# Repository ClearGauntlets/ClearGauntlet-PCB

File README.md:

# ClearGauntlet-PCB
PCB - Schematics Design for VR Gloves

A breakout board for ClearGauntlets, aimed at improving cable management and minifying electronics of VR Gloves.

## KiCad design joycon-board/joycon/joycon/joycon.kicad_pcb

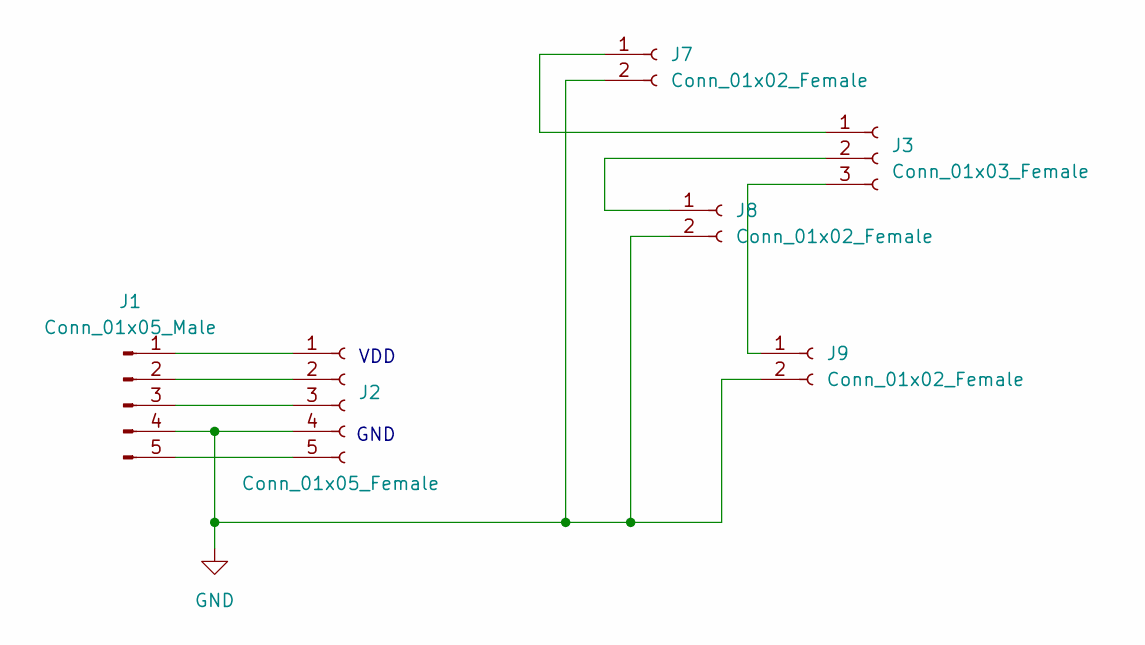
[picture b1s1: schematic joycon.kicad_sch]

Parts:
J1: Conn_01x05_Male; 5034800540
J2: Conn_01x05_Female; PinSocket_1x05_P2.54mm_Vertical
J3: Conn_01x03_Female; PinSocket_1x03_P2.54mm_Vertical
J7, J8, J9: Conn_01x02_Female; PinSocket_1x02_P2.54mm_Vertical

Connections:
GND: J1.4, J2.4, J7.2, J8.2, J9.2
unnamed: J1.1, J2.1
unnamed: J1.2, J2.2
unnamed: J1.3, J2.3
unnamed: J1.5, J2.5
unnamed: J3.1, J7.1
unnamed: J3.2, J8.1
unnamed: J3.3, J9.1

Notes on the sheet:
GND
VDD

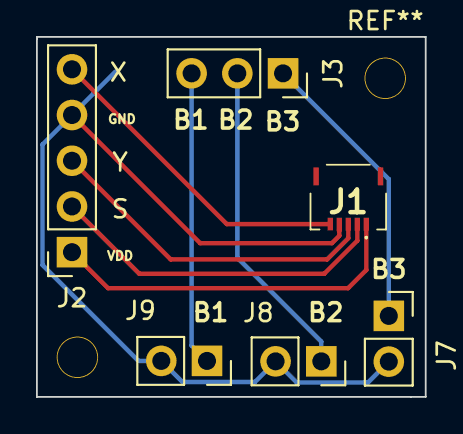
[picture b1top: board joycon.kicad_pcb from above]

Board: 2 copper layers, 21.6 x 20.0 mm, 6 parts (0 on the bottom side), 8 nets.

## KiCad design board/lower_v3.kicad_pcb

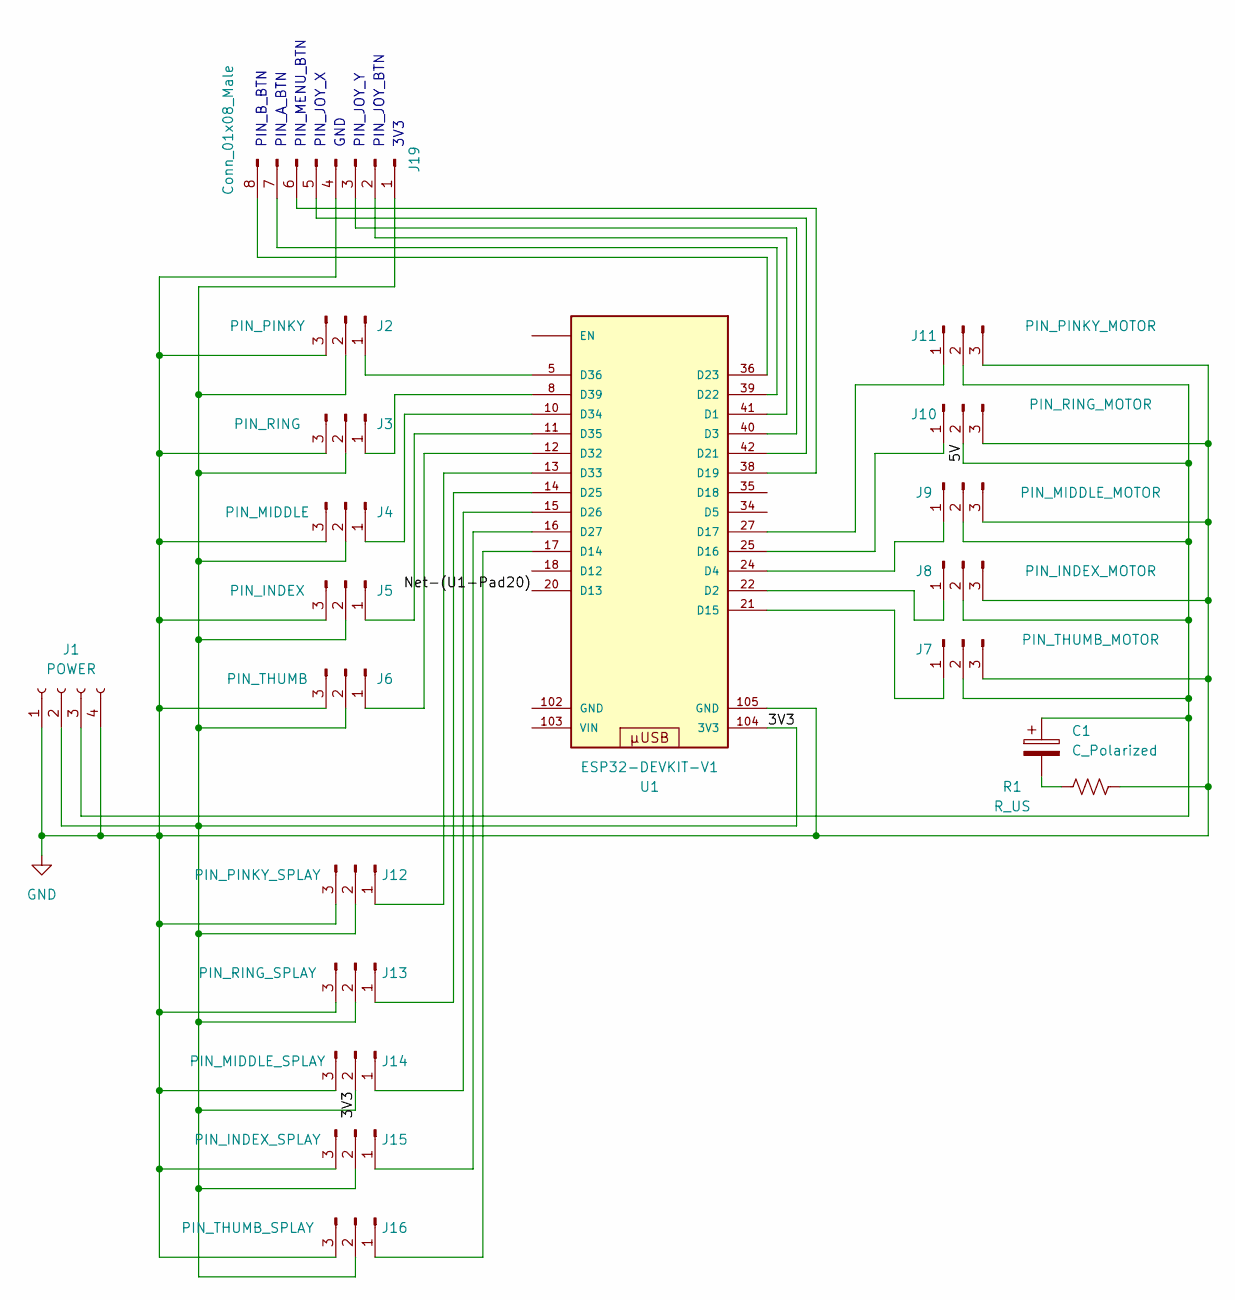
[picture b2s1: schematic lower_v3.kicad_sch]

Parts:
C1: C_Polarized; CP_Radial_D10.0mm_P5.00mm
J1: POWER; JST_EH_B4B-EH-A_1x04_P2.50mm_Vertical
J2: PIN_PINKY; PinHeader_1x03_P2.54mm_Vertical
J3: PIN_RING; PinHeader_1x03_P2.54mm_Vertical
J4: PIN_MIDDLE; PinHeader_1x03_P2.54mm_Vertical
J5: PIN_INDEX; PinHeader_1x03_P2.54mm_Vertical
J6: PIN_THUMB; PinHeader_1x03_P2.54mm_Vertical
J7: PIN_THUMB_MOTOR; PinHeader_1x03_P2.54mm_Vertical
J8: PIN_INDEX_MOTOR; PinHeader_1x03_P2.54mm_Vertical
J9: PIN_MIDDLE_MOTOR; PinHeader_1x03_P2.54mm_Vertical
J10: PIN_RING_MOTOR; PinHeader_1x03_P2.54mm_Vertical
J11: PIN_PINKY_MOTOR; PinHeader_1x03_P2.54mm_Vertical
J12: PIN_PINKY_SPLAY; PinHeader_1x03_P2.54mm_Vertical
J13: PIN_RING_SPLAY; PinHeader_1x03_P2.54mm_Vertical
J14: PIN_MIDDLE_SPLAY; PinHeader_1x03_P2.54mm_Vertical
J15: PIN_INDEX_SPLAY; PinHeader_1x03_P2.54mm_Vertical
J16: PIN_THUMB_SPLAY; PinHeader_1x03_P2.54mm_Vertical
J19: Conn_01x08_Male; PinSocket_2x04_P2.54mm_Vertical
R1: R_US; R_Axial_DIN0207_L6.3mm_D2.5mm_P10.16mm_Horizontal
U1: ESP32-DEVKIT-V1; MODULE_ESP32_DEVKIT_V1; PARTREV N/A

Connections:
/3V3: J1.2, J2.2, J3.2, J4.2, J5.2, J6.2, J12.2, J13.2, J14.2, J15.2, J16.2, J19.1, U1.104 (3V3)
/5V: C1.1, J1.3, J7.2, J8.2, J9.2, J10.2, J11.2
/Net-(U1-Pad20): U1.20 (D13)
GND: J1.1, J1.4, J2.3, J3.3, J4.3, J5.3, J6.3, J7.3, J8.3, J9.3, J10.3, J11.3, J12.3, J13.3, J14.3, J15.3, J16.3, J19.4, R1.1, U1.105 (GND)
unnamed: C1.2, R1.2
unnamed: J2.1, U1.5 (D36)
unnamed: J3.1, U1.8 (D39)
unnamed: J4.1, U1.10 (D34)
unnamed: J5.1, U1.11 (D35)
unnamed: J6.1, U1.12 (D32)
unnamed: J7.1, U1.21 (D15)
unnamed: J8.1, U1.22 (D2)
unnamed: J9.1, U1.24 (D4)
unnamed: J10.1, U1.25 (D16)
unnamed: J11.1, U1.27 (D17)
unnamed: J12.1, U1.13 (D33)
unnamed: J13.1, U1.14 (D25)
unnamed: J14.1, U1.15 (D26)
unnamed: J15.1, U1.16 (D27)
unnamed: J16.1, U1.17 (D14)
unnamed: J19.2, U1.41 (D1)
unnamed: J19.3, U1.40 (D3)
unnamed: J19.5, U1.42 (D21)
unnamed: J19.6, U1.38 (D19)
unnamed: J19.7, U1.39 (D22)
unnamed: J19.8, U1.36 (D23)

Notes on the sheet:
PIN_JOY_Y
PIN_A_BTN
PIN_JOY_X
PIN_MENU_BTN
GND
PIN_JOY_BTN
3V3
PIN_B_BTN

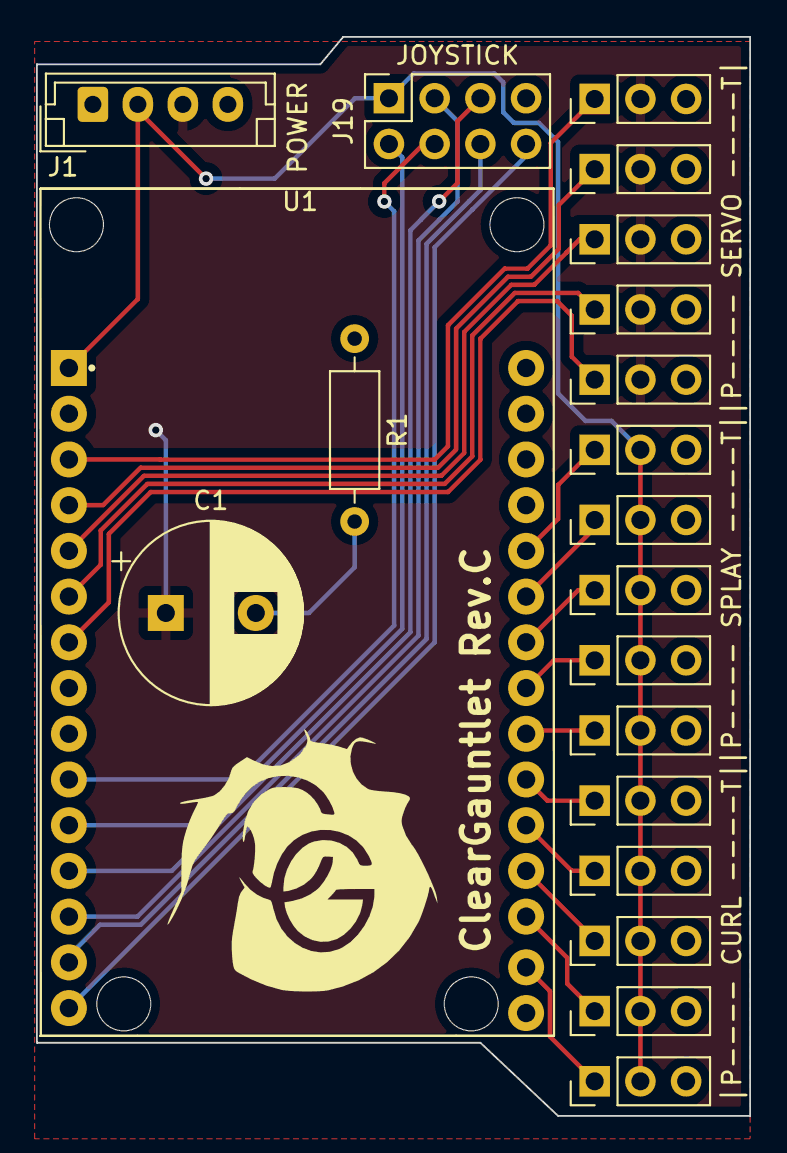
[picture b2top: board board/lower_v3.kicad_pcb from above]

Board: 2 copper layers, 39.6 x 59.9 mm, 20 parts (0 on the bottom side), 25 nets.

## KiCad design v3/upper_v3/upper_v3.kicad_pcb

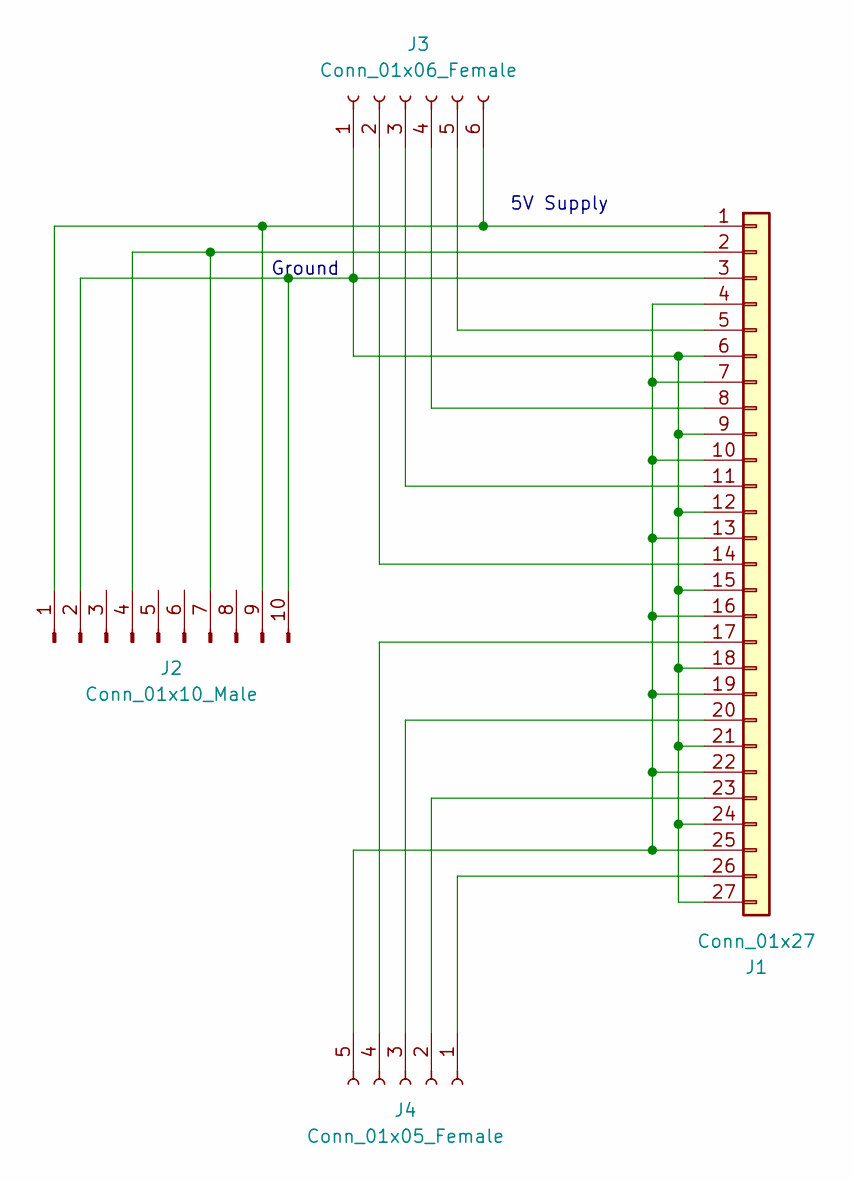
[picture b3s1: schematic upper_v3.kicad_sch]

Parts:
J1: Conn_01x27; PinHeader_1x27_P2.54mm_Horizontal
J2: Conn_01x10_Male; PinHeader_1x10_P2.54mm_Vertical
J3: Conn_01x06_Female; PinSocket_1x06_P2.54mm_Vertical
J4: Conn_01x05_Female; PinSocket_1x05_P2.54mm_Vertical

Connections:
unnamed: J1.1, J2.1, J2.9, J3.6
unnamed: J1.2, J2.4, J2.7
unnamed: J1.5, J3.5
unnamed: J1.8, J3.4
unnamed: J1.4, J1.7, J1.10, J1.13, J1.16, J1.19, J1.22, J1.25, J4.5
unnamed: J1.11, J3.3
unnamed: J1.3, J1.6, J1.9, J1.12, J1.15, J1.18, J1.21, J1.24, J1.27, J2.2, J2.10, J3.1
unnamed: J1.14, J3.2
unnamed: J1.17, J4.4
unnamed: J1.20, J4.3
unnamed: J1.23, J4.2
unnamed: J1.26, J4.1

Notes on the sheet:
Ground
5V Supply

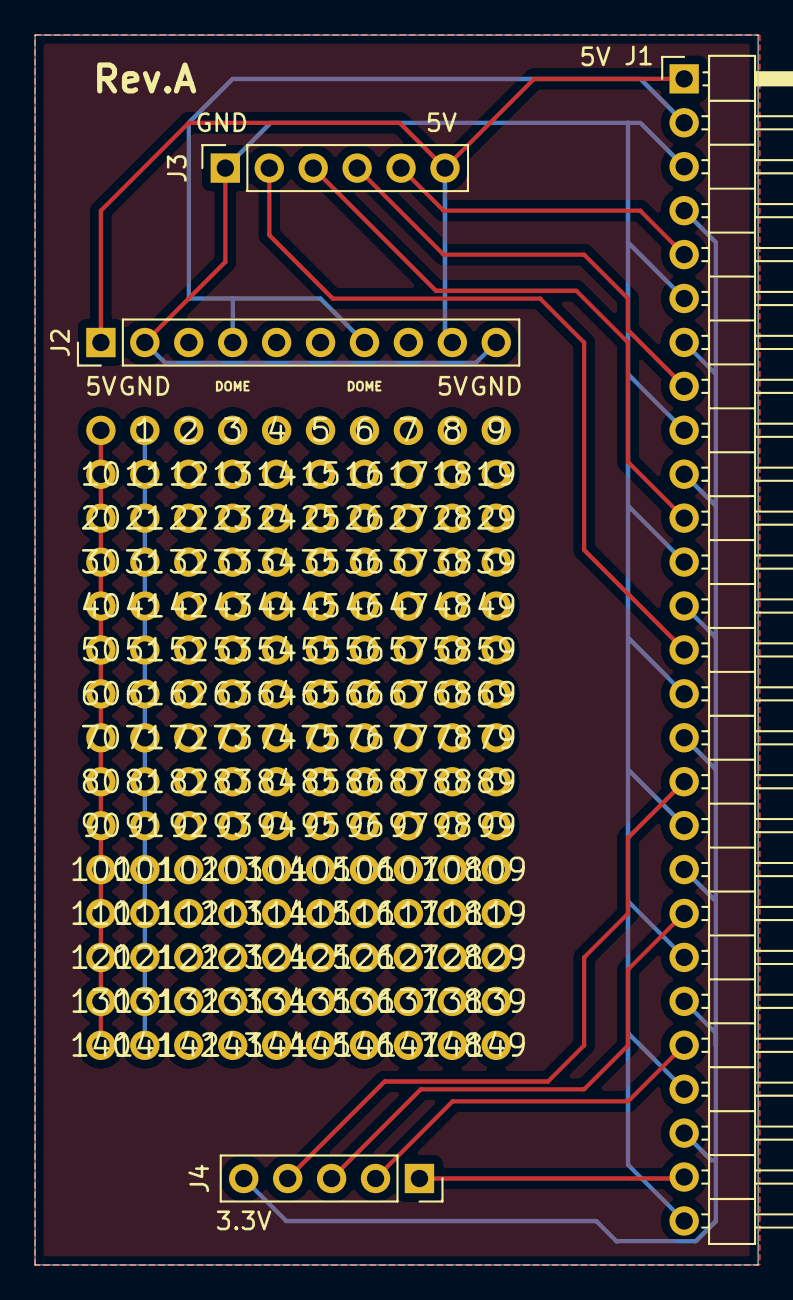
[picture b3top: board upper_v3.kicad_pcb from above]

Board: 2 copper layers, 41.8 x 71.1 mm, 153 parts (0 on the bottom side), 12 nets.

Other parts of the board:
1, 2, 3, 4, 5, 6, 7, 8, 9, 10, 11, 12, 13, 14, 15, 16, 17, 18, 19, 20, 21, 22, 23, 24, 25, 26, 27, 28, 29, 30, 31, 32, 33, 34, 35, 36, 37, 38, 39, 40, 41, 42, 43, 44, 45, 46, 47, 48, 49, 50, 51, 52, 53, 54, 55, 56, 57, 58, 59, 60, 61, 62, 63, 64, 65, 66, 67, 68, 69, 70, 71, 72, 73, 74, 75, 76, 77, 78, 79, 80, 81, 82, 83, 84, 85, 86, 87, 88, 89, 90, 91, 92, 93, 94, 95, 96, 97, 98, 99, 100, 101, 102, 103, 104, 105, 106, 107, 108, 109, 110, 111, 112, 113, 114, 115, 116, 117, 118, 119, 120, 121, 122, 123, 124, 125, 126, 127, 128, 129, 130, 131, 132, 133, 134, 135, 136, 137, 138, 139, 140, 141, 142, 143, 144, 145, 146, 147, 148, 149: (no value)

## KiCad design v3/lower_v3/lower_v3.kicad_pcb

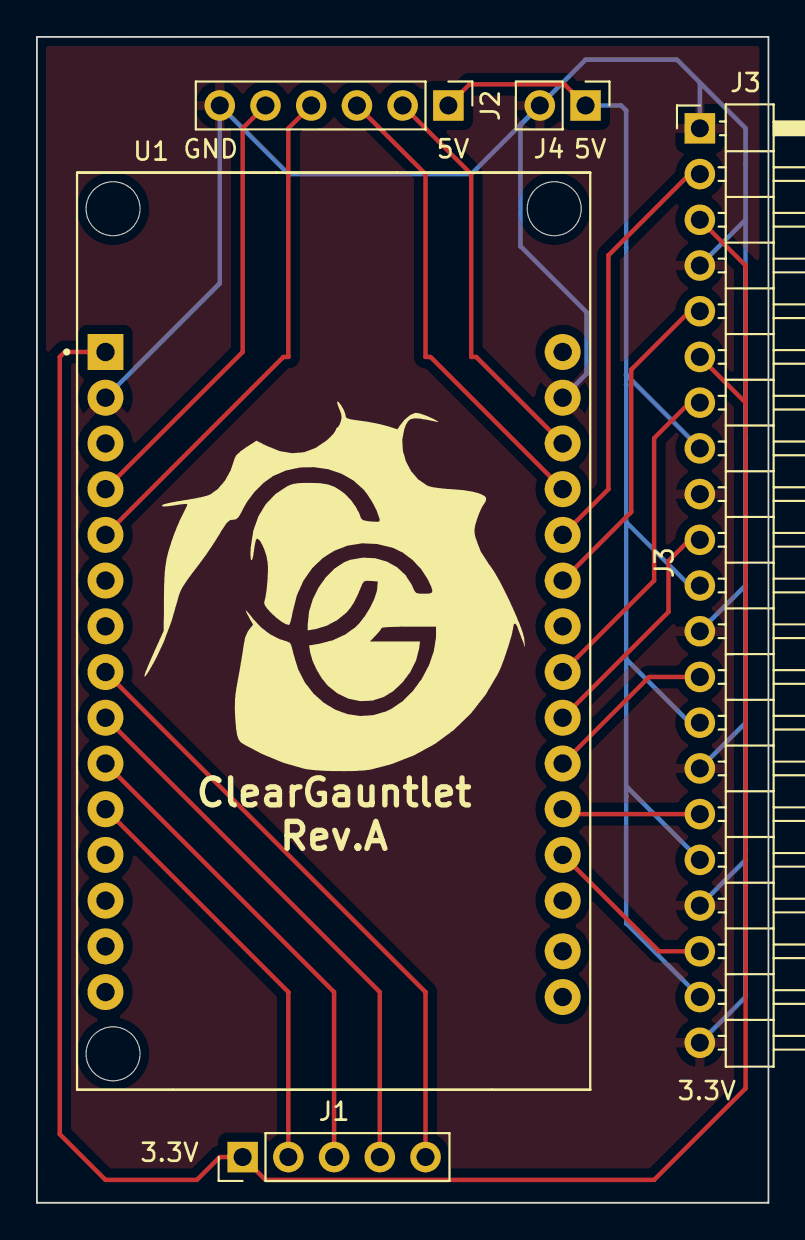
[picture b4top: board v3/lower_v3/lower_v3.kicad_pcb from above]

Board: 2 copper layers, 40.6 x 64.8 mm, 6 parts (0 on the bottom side), 18 nets.

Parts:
J1: Conn_01x05_Male; PinHeader_1x05_P2.54mm_Vertical
J2: Conn_01x06_Male; PinHeader_1x06_P2.54mm_Vertical
J3: Conn_01x21; PinHeader_1x21_P2.54mm_Horizontal
J4: Conn_01x02_Male; PinHeader_1x02_P2.54mm_Vertical
U1: ESP32-DEVKIT-V1; MODULE_ESP32_DEVKIT_V1
logo: LOGO; logo-big

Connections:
GND: J2.6, J3.1, J3.4, J3.9, J3.12, J3.15, J3.18, J3.21, J4.2, U1.2 (GND), U1.29 (GND)
unnamed: J1.1, J3.3, J3.6, U1.1 (3V3)
unnamed: J1.2, U1.11 (D21)
unnamed: J1.3, U1.10 (D19)
unnamed: J1.4, U1.9 (D18)
unnamed: J1.5, U1.8 (D5)
unnamed: J3.2, U1.26 (D14)
unnamed: J3.5, U1.25 (D27)
unnamed: J3.7, U1.23 (D25)
unnamed: J3.10, U1.22 (D33)
unnamed: J2.1, J3.8, J3.11, J3.14, J3.17, J3.20, J4.1
unnamed: J3.13, U1.21 (D32)
unnamed: J3.16, U1.20 (D35)
unnamed: J3.19, U1.19 (D34)
unnamed: J2.5, U1.4 (D2)
unnamed: J2.4, U1.5 (D4)
unnamed: J2.3, U1.27 (D12)
unnamed: J2.2, U1.28 (D13)

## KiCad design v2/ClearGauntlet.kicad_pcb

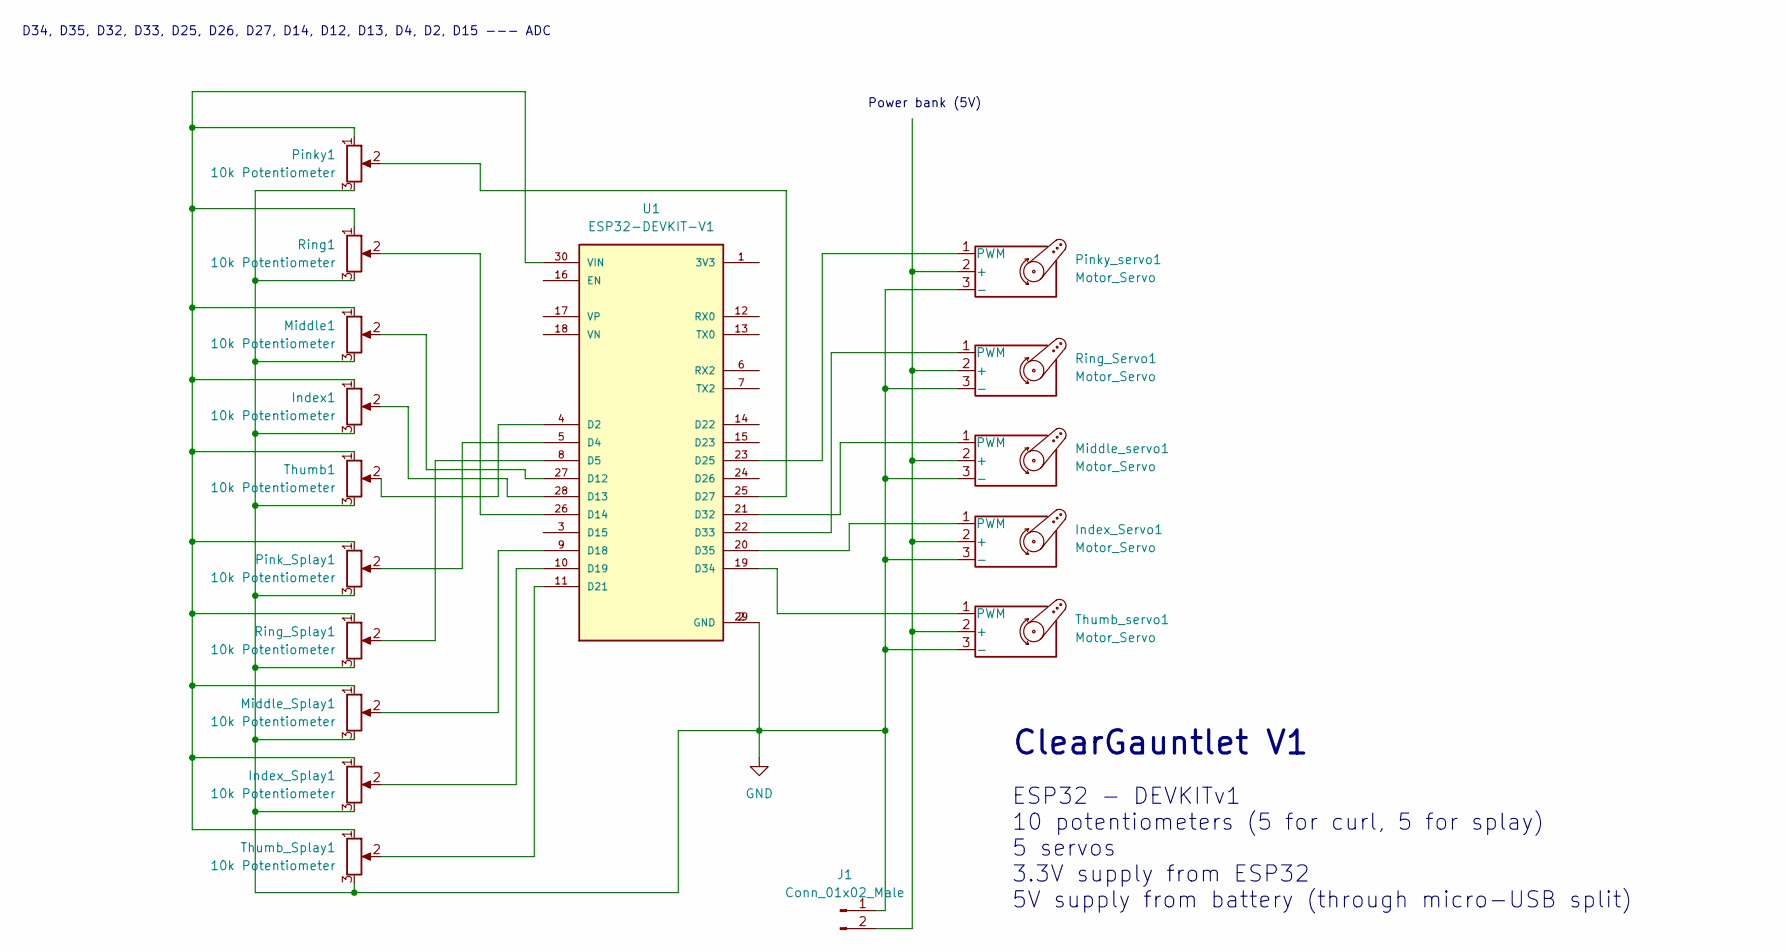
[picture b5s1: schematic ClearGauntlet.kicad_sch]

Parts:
Index1: 10k Potentiometer; PinHeader_1x03_P2.54mm_Vertical
Index_Servo1: Motor_Servo; PinHeader_1x03_P2.54mm_Vertical
Index_Splay1: 10k Potentiometer; PinHeader_1x03_P2.54mm_Vertical
J1: Conn_01x02_Male; PinHeader_1x02_P2.54mm_Vertical
Middle1: 10k Potentiometer; PinHeader_1x03_P2.54mm_Vertical
Middle_Splay1: 10k Potentiometer; PinHeader_1x03_P2.54mm_Vertical
Middle_servo1: Motor_Servo; PinHeader_1x03_P2.54mm_Vertical
Pink_Splay1: 10k Potentiometer; PinHeader_1x03_P2.54mm_Vertical
Pinky1: 10k Potentiometer; PinHeader_1x03_P2.54mm_Vertical
Pinky_servo1: Motor_Servo; PinHeader_1x03_P2.54mm_Vertical
Ring1: 10k Potentiometer; PinHeader_1x03_P2.54mm_Vertical
Ring_Servo1: Motor_Servo; PinHeader_1x03_P2.54mm_Vertical
Ring_Splay1: 10k Potentiometer; PinHeader_1x03_P2.54mm_Vertical
Thumb1: 10k Potentiometer; PinHeader_1x03_P2.54mm_Vertical
Thumb_Splay1: 10k Potentiometer; PinHeader_1x03_P2.54mm_Vertical
Thumb_servo1: Motor_Servo; PinHeader_1x03_P2.54mm_Vertical
U1: ESP32-DEVKIT-V1; MODULE_ESP32_DEVKIT_V1; PARTREV N/A

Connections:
GND: Index1.3, Index_Servo1.3 (-), Index_Splay1.3, J1.1, Middle1.3, Middle_Splay1.3, Middle_servo1.3 (-), Pink_Splay1.3, Pinky1.3, Pinky_servo1.3 (-), Ring1.3, Ring_Servo1.3 (-), Ring_Splay1.3, Thumb1.3, Thumb_Splay1.3, Thumb_servo1.3 (-), U1.2 (GND), U1.29 (GND)
unnamed: Index1.1, Index_Splay1.1, Middle1.1, Middle_Splay1.1, Pink_Splay1.1, Pinky1.1, Ring1.1, Ring_Splay1.1, Thumb1.1, Thumb_Splay1.1, U1.30 (VIN)
unnamed: Index1.2, U1.28 (D13)
unnamed: Index_Servo1.1 (PWM), U1.20 (D35)
unnamed: Index_Servo1.2 (+), J1.2, Middle_servo1.2 (+), Pinky_servo1.2 (+), Ring_Servo1.2 (+), Thumb_servo1.2 (+)
unnamed: Index_Splay1.2, U1.10 (D19)
unnamed: Middle1.2, U1.27 (D12)
unnamed: Middle_Splay1.2, U1.9 (D18)
unnamed: Middle_servo1.1 (PWM), U1.21 (D32)
unnamed: Pink_Splay1.2, U1.5 (D4)
unnamed: Pinky1.2, U1.25 (D27)
unnamed: Pinky_servo1.1 (PWM), U1.23 (D25)
unnamed: Ring1.2, U1.26 (D14)
unnamed: Ring_Servo1.1 (PWM), U1.22 (D33)
unnamed: Ring_Splay1.2, U1.8 (D5)
unnamed: Thumb1.2, U1.4 (D2)
unnamed: Thumb_Splay1.2, U1.11 (D21)
unnamed: Thumb_servo1.1 (PWM), U1.19 (D34)

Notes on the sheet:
D34, D35, D32, D33, D25, D26, D27, D14, D12, D13, D4, D2, D15 --- ADC
ClearGauntlet V1
ESP32 - DEVKITv1 10 potentiometers (5 for curl, 5 for splay) 5 servos 3.3V supply from ESP32 5V supply from battery (through micro-USB split)
Power bank (5V)

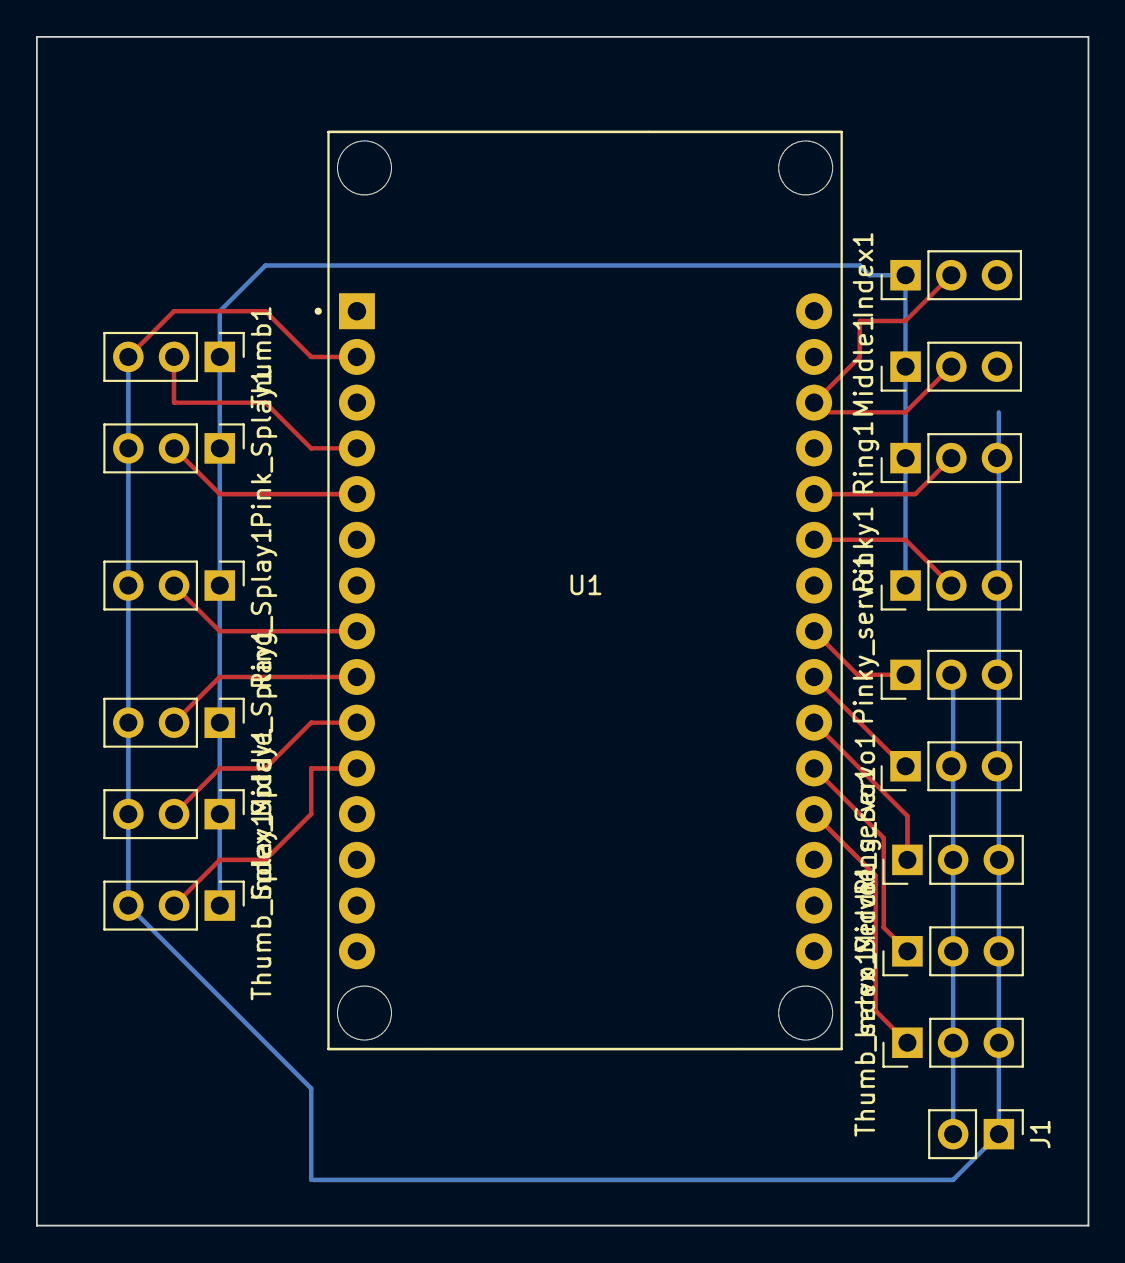
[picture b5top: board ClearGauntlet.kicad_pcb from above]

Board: 2 copper layers, 58.4 x 66.0 mm, 17 parts (0 on the bottom side), 18 nets.

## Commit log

2022-10-17 Add files via upload
    initial commit
2022-10-17 PCB updated with footprint
2022-10-17 Add gitignore
2022-10-17 Create protoboard dir
2022-10-17 Schematics
2022-10-17 adding PCB updated with schematics
2022-10-18 dingus
2022-10-24 PCB with wiring
2022-10-26 Check autosaves
2022-11-06 adding v3
2022-11-14 Complete Toast PCB
2022-11-19 Adding clear Proto-board portion for the DOME
2022-11-19 Rev.A Toast Design, fixing connection between 2 boards, adding 3 I/O for the DOME, creating blank proto area for testing
2022-11-22 With OshPark order
2022-11-23 Add pin detail, fixing layout annotation on board
2023-01-29 Lay out protoboard PCB
2023-01-30 Add more pins
2023-01-31 Finalize board
2023-01-31 Submit Rev B for fabrication
2023-02-01 Create README.md for rev A
    Move from the main
2023-02-01 Rev C
2023-02-06 README updated
2023-02-10 Locate OpAmp and Photo Diodes
2023-02-15 add joycon pcb
2023-03-08 joystick-PCB
2023-03-08 Combine joystick connector, add C and R
2023-03-08 RevC RC 1
2023-03-08 Rev C RC 1.1
    Oops wanted to make absolutely sure the ground and 5V planes were
    properly connected
2023-03-08 Smallerize resistor
2023-03-08 Fix Joystick port pin layout
2023-03-08 Remove via
2023-03-09 Stub out README for Rev C
2023-05-01 Joystick PCB design
